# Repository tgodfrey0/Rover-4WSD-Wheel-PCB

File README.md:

# Rover 4WSD Wheel PCB

This repository contains the KiCAD design files for a 4-wheel steering and driving rover. The HardwareX paper can be found [here](https://github.com/tgodfrey0/Rover-4WSD-Wheel-PCB).

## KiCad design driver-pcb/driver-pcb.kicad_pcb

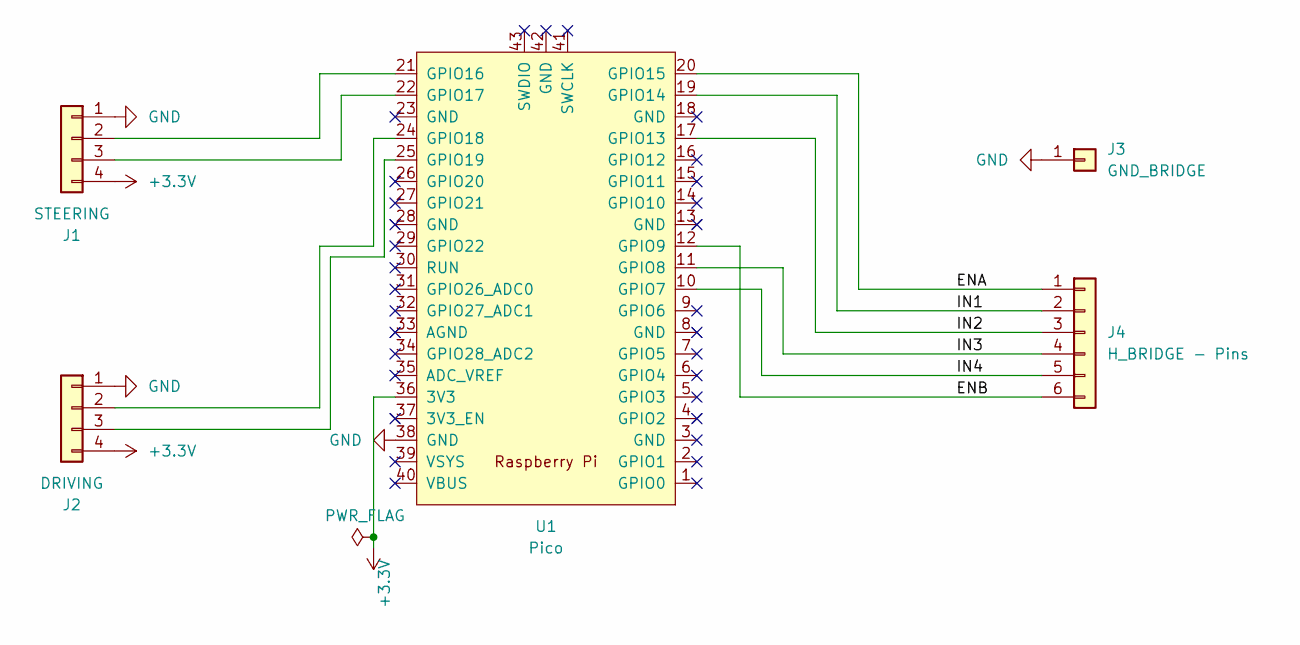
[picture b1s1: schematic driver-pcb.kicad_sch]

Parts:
J1: STEERING; PinHeader_1x04_P2.54mm_Vertical
J2: DRIVING; PinHeader_1x04_P2.54mm_Vertical
J3: GND_BRIDGE; PinHeader_1x01_P2.54mm_Vertical
J4: H_BRIDGE - Pins; PinHeader_1x06_P2.54mm_Vertical
U1: Pico; RPi_Pico_SMD_TH

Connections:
+3.3V: J1.4, J2.4, U1.36 (3V3)
/ENA: J4.1, U1.20 (GPIO15)
/ENB: J4.6, U1.12 (GPIO9)
/IN1: J4.2, U1.19 (GPIO14)
/IN2: J4.3, U1.17 (GPIO13)
/IN3: J4.4, U1.11 (GPIO8)
/IN4: J4.5, U1.10 (GPIO7)
GND: J1.1, J2.1, J3.1, U1.38 (GND)
unnamed: J1.2, U1.21 (GPIO16)
unnamed: J1.3, U1.22 (GPIO17)
unnamed: J2.2, U1.24 (GPIO18)
unnamed: J2.3, U1.25 (GPIO19)

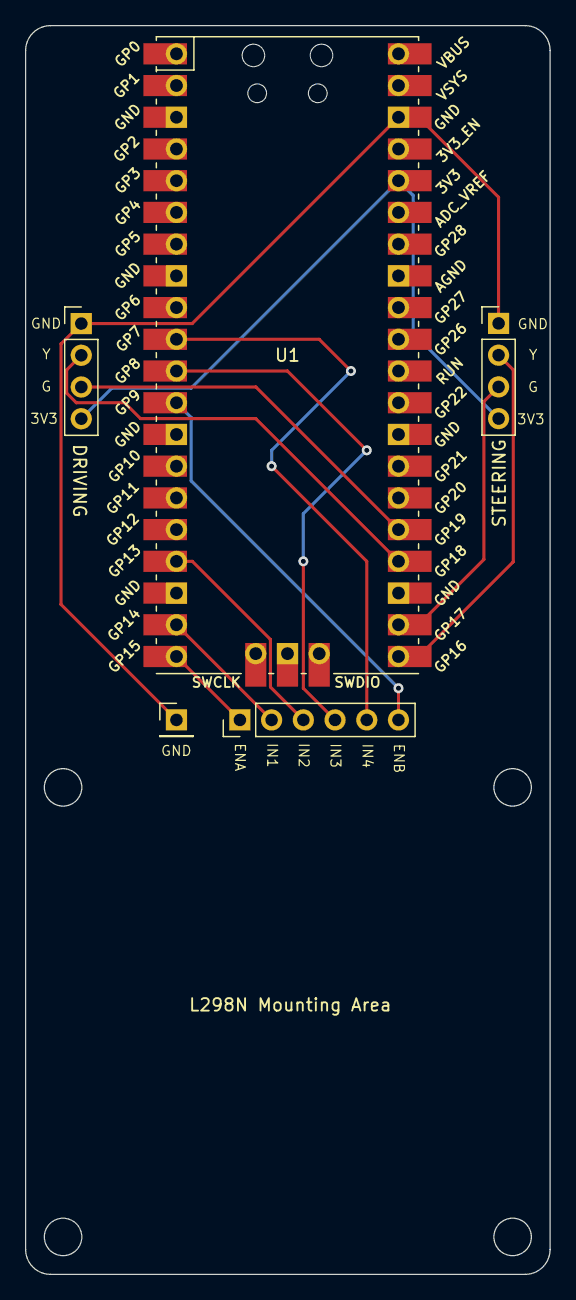
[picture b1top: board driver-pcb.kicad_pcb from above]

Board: 2 copper layers, 42.0 x 100.0 mm, 5 parts (0 on the bottom side), 12 nets.

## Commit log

2023-08-09 pcbs
2023-08-09 license and readme
